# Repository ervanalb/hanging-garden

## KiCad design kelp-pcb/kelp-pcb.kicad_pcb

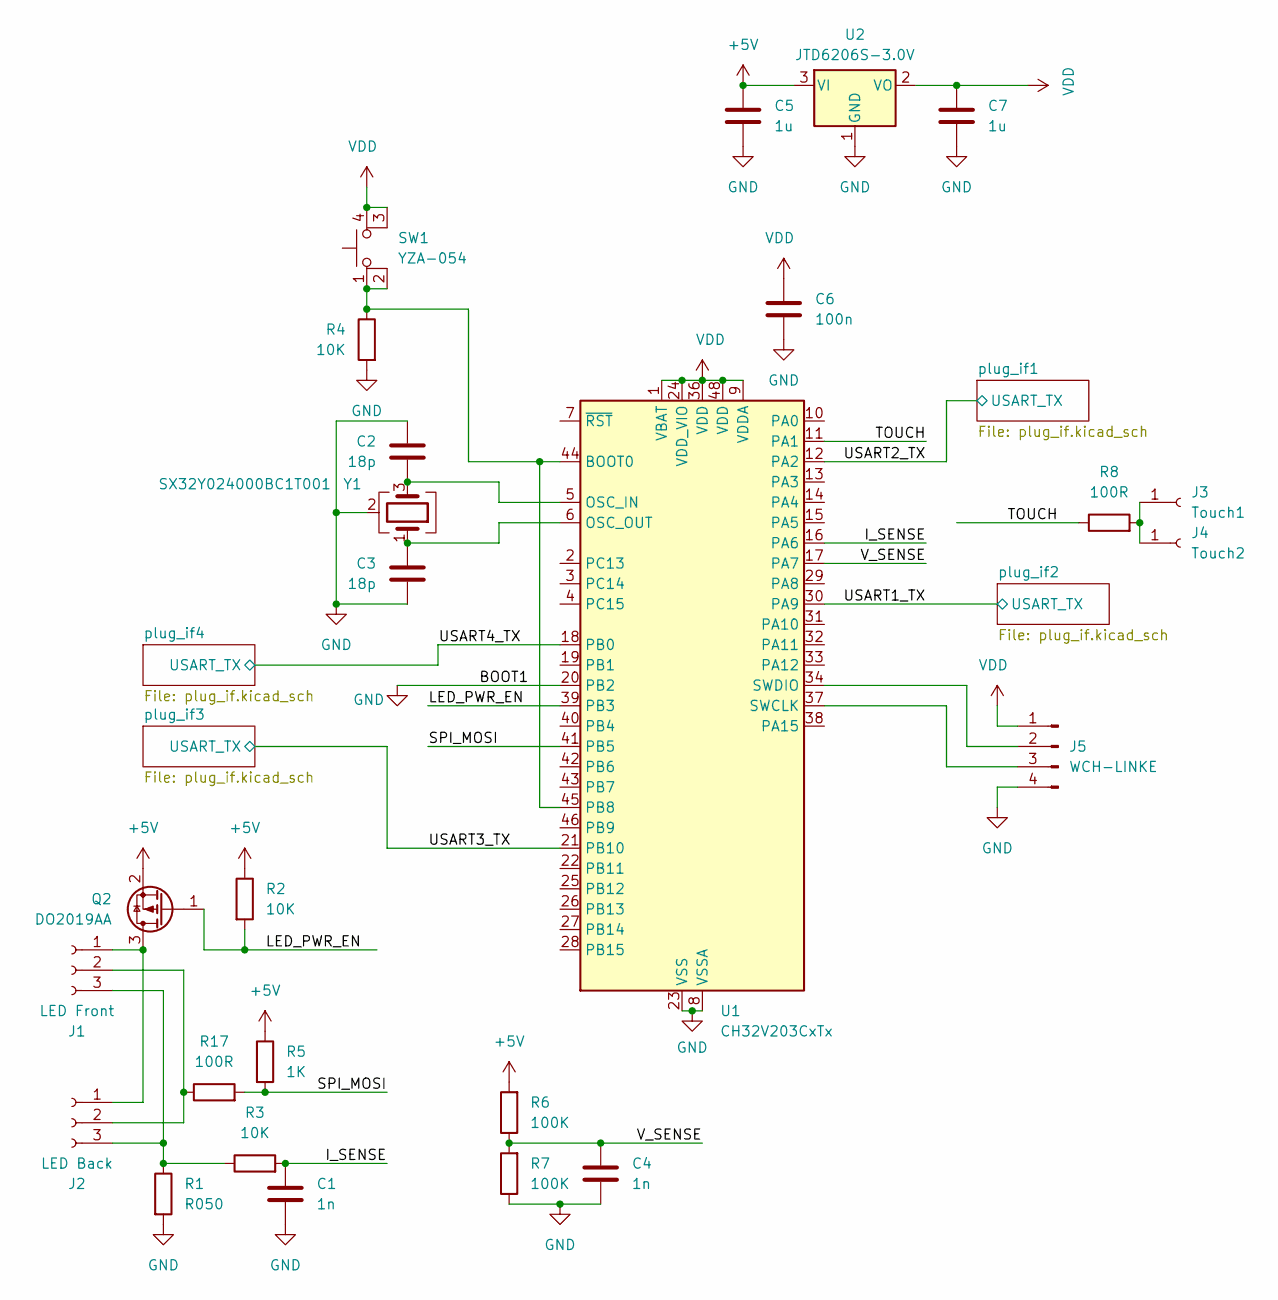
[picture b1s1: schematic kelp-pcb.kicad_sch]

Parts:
C1, C4: 1n; C_0402_1005Metric
C2, C3: 18p; C_0402_1005Metric
C5, C7: 1u; C_0603_1608Metric
C6: 100n; C_0402_1005Metric
J1: LED Front; led_strip
J2: LED Back; led_strip
J3: Touch1; sew_pad
J4: Touch2; sew_pad
J5: WCH-LINKE; PinHeader_1x04_P2.54mm_Vertical
Q2: DO2019AA; SOT-23
R1: R050; R_1206_3216Metric
R2, R3, R4: 10K; R_0402_1005Metric
R5: 1K; R_0402_1005Metric
R6, R7: 100K; R_0402_1005Metric
R8, R17: 100R; R_0402_1005Metric
SW1: YZA-054
U1: CH32V203CxTx; QFN-48-1EP_7x7mm_P0.5mm_EP5.3x5.3mm
U2: JTD6206S-3.0V; SOT-23-3
Y1: SX32Y024000BC1T001; Crystal_SMD_3225-4Pin_3.2x2.5mm

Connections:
+5V: C5.1, Q2.2 (S), R2.1, R5.1, R6.2, U2.3 (VI); also elsewhere on the board
/I_SENSE: C1.1, R3.2, U1.16 (PA6)
/LED_PWR_EN: Q2.1 (G), R2.2, U1.39 (PB3)
/SPI_MOSI: R5.2, R17.2, U1.41 (PB5)
/TOUCH: R8.1, U1.11 (PA1)
/USART1_TX: U1.30 (PA9); also elsewhere on the board
/USART2_TX: U1.12 (PA2); also elsewhere on the board
/USART3_TX: U1.21 (PB10); also elsewhere on the board
/USART4_TX: U1.18 (PB0); also elsewhere on the board
/V_SENSE: C4.1, R6.1, R7.2, U1.17 (PA7)
GND: C1.2, C2.1, C3.2, C4.2, C5.2, C6.2, C7.2, J5.4, R1.2, R4.2, R7.1, U1.8 (VSSA), U1.20 (PB2), U1.23 (VSS), U1.35 (VSS), U1.47 (VSS), U2.1 (GND), Y1.2 (G), Y1.4 (G); also elsewhere on the board
unnamed: J1.1, J2.1, Q2.3 (D)
unnamed: J1.2, J2.2, R17.1
unnamed: J1.3, J2.3, R1.1, R3.1
unnamed: J3.1 (Pin_1_1), J4.1 (Pin_1_1), R8.2
unnamed: J5.2, U1.34 (SWDIO)
unnamed: J5.3, U1.37 (SWCLK)
unnamed: R4.1, SW1.1, SW1.2, U1.44 (BOOT0), U1.45 (PB8)
unnamed: C2.2, U1.5 (OSC_IN), Y1.3
unnamed: C3.1, U1.6 (OSC_OUT), Y1.1
VDD: C6.1, C7.1, J5.1, SW1.3 (K), SW1.4 (A), U1.1 (VBAT), U1.9 (VDDA), U1.24 (VDD_VIO), U1.36 (VDD), U1.48 (VDD), U2.2 (VO); also elsewhere on the board

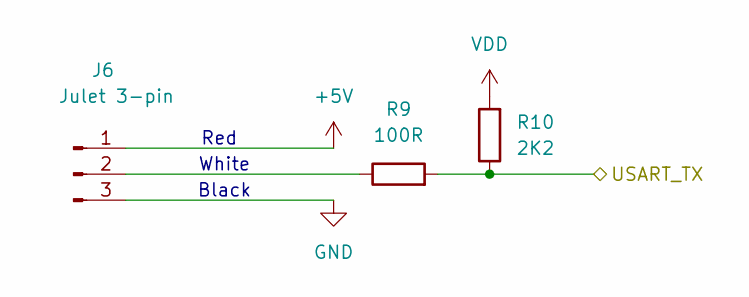
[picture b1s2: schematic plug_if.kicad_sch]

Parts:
J6: Julet 3-pin; julet_3pin
R9: 100R; R_0402_1005Metric
R10: 2K2; R_0402_1005Metric

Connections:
+5V: J6.1; also elsewhere on the board
/USART2_TX: R9.2, R10.1; also elsewhere on the board
GND: J6.3; also elsewhere on the board
unnamed: J6.2, R9.1
VDD: R10.2; also elsewhere on the board

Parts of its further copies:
J7, J8, J9: Julet 3-pin; julet_3pin
R11, R13, R15: 100R; R_0402_1005Metric
R12, R14, R16: 2K2; R_0402_1005Metric

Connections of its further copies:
+5V: J7.1, J8.1, J9.1; also elsewhere on the board
/USART1_TX: R11.2, R12.1; also elsewhere on the board
/USART3_TX: R13.2, R14.1; also elsewhere on the board
/USART4_TX: R15.2, R16.1; also elsewhere on the board
GND: J7.3, J8.3, J9.3; also elsewhere on the board
unnamed: J7.2, R11.1
unnamed: J8.2, R13.1
unnamed: J9.2, R15.1
VDD: R12.2, R14.2, R16.2; also elsewhere on the board

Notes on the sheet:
White
Black
Red

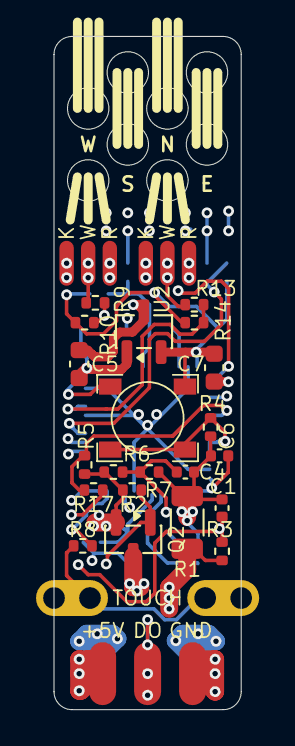
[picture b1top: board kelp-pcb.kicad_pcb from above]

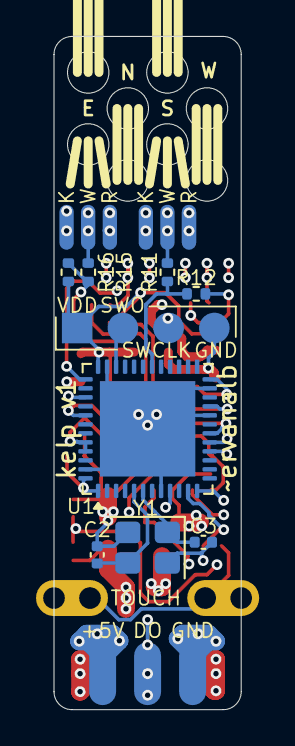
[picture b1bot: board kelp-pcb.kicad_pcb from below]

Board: 4 copper layers, 10.4 x 37.4 mm, 38 parts (12 on the bottom side), 25 nets.

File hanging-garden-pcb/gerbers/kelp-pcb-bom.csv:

Comment,Designator,Footprint,JLCPCB Part #(optional)
1n,"C1, C4",C_0402_1005Metric,C1523
18p,"C2, C3",C_0402_1005Metric,C1549
1u,"C5, C7",C_0603_1608Metric,C1592
100n,C6,C_0402_1005Metric,C1525
DO2019AA,Q2,SOT-23,C54349765
R050,R1,R_1206_3216Metric,C7419998
10K,"R2, R3, R4",R_0402_1005Metric,C60490
1K,R5,R_0402_1005Metric,C11702
100K,"R6, R7",R_0402_1005Metric,C25741
100R,"R8, R9, R11, R13, R15, R17",R_0402_1005Metric,C25076
2K2,"R10, R12, R14, R16",R_0402_1005Metric,C25879
YZA-054,SW1,YZA-054,C49339754
CH32V203CxTx,U1,QFN-48-1EP_7x7mm_P0.5mm_EP5.3x5.3mm,C6407762
JTD6206S-3.0V,U2,SOT-23-3,C49308288
SX32Y024000BC1T001,Y1,Crystal_SMD_3225-4Pin_3.2x2.5mm,C7420736

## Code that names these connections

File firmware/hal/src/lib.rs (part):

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            riscv::asm::delay(100000);
        }

        // PA1, PA6 and PA7 are ADC inputs
        // PA1: Touch key detection (ADC2_IN1)
        // PA6: Current sensor (ADC1_IN6)
        // PA7: Voltage sensor (ADC1_IN7)
        // Configure as analog inputs
        pac::GPIOA.cfglr().modify(|w| {
            w.set_mode(1, Mode::INPUT);
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            w.set_cnf(7, Cnf::ANALOG_IN__PUSH_PULL_OUT);
        });

        // PB3 enables LED power when high
        // Start with it HIGH (power disabled)
        pac::GPIOB.bshr().write(|w| w.set_bs(3, true));
        compiler_fence(Ordering::SeqCst);
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        });

        // Configure SPI1 pins for WS2812 output
        // PB5: MOSI
        pac::GPIOB.cfglr().modify(|w| {
            w.set_mode(5, Mode::OUTPUT_50MHZ);
            w.set_cnf(5, Cnf::AF_OPEN_DRAIN_OUT);
        });
        // SPI1_RM=1 in order to use PB5
        pac::AFIO.pcfr1().modify(|w| {
            w.set_spi1_rm(true);
        });
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
        // Initialize all 4 USARTs in half-duplex mode at 1 Mbaud
        unsafe {
            // USART1: PA9, DMA1_CH4 (TX), DMA1_CH5 (RX)
            init_usart_halfduplex(
                pac::USART1,
                pac::GPIOA,
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                &mut USART1_RX_DMA_BUFFER,
            );

            // USART2: PA2, DMA1_CH7 (TX), DMA1_CH6 (RX)
            init_usart_halfduplex(
                pac::USART2,
                pac::GPIOA,
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                &mut USART2_RX_DMA_BUFFER,
            );

            // USART3: PB10, DMA1_CH2 (TX), DMA1_CH3 (RX)
            init_usart_halfduplex(
                pac::USART3,
                pac::GPIOB,
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                &mut USART3_RX_DMA_BUFFER,
            );

            // USART4: PB0, DMA1_CH1 (TX), DMA1_CH8 (RX)
            init_usart_halfduplex(
                pac::USART4,
                pac::GPIOB,
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        // Set sequence length to 1 (single channel conversion)
        pac::ADC2.rsqr1().modify(|w| w.set_l(0)); // 1 conversion

        // Set channel 1 (PA1) in the first position of the regular sequence
        pac::ADC2.rsqr3().modify(|w| w.set_sq(0, 1));

        // Set charge offset time
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pub struct Touch {}

impl Touch {
    /// Read touch key value from PA1 (ADC2_IN1)
    ///
    /// Returns the ADC value representing the capacitance.
    /// Lower values typically indicate a touch event.
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        }
    }

    /// Read current sensor on PA6 (ADC6)
    /// Returns raw ADC value (0-4095 for 12-bit ADC)
    pub async fn read_current(&mut self) -> u16 {
        self.read_adc_channel(6).await
    }

    /// Read voltage sensor on PA7 (ADC7)
    /// Returns raw ADC value (0-4095 for 12-bit ADC)
    pub async fn read_voltage(&mut self) -> u16 {
        self.read_adc_channel(7).await
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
